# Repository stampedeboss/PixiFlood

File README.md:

# PixiFlood
PixiFlood LED Driver, Turn a 10w-100w floodlight Housing into a WS2811 Floodlight Pixel

DESCRIPTION:

A LED Driver that will allow a flood light to be controlled as a WS2811 Pixel. Allows up to 
170 flood lights to be controlled with a single universe. 

My goal was to enable placement of a flood light without having to deal with different controllers or 
wiring needs. By using WS2811, place a flood light at the beginning or end of a pixel string and maintain 
complete control. 

Version 2 and Version 3 introduced the concept of a built in ESPixelStick, which allows wireless connectitivy to communicate with the Floodlight.

Version 3:
Focused on delivering a single board designed to support any wattage of LED from 10w to 100w.
This objective required the design to no longer include direct attachment of the LED to the PCB, it is to 
be connected via wires to allow for the wide arrangement of LED sizes and pin spacings.

The previous designs relied on linear voltage regulators since the voltage reduction was acceptable going 
from 12v to 5v.  With the use of higher wattage LEDs, voltage requirements are much greater required changing
the 5v voltage regulator circuitry to a switching model to eliminate the overheating of the previous design.

The PT4115 specifications are unacceptable to anything above a 20w LED, as such beginning with 3.0 the LED
Driver is being switched out for an AL8862 and the supporting components have been modified to support that
new IC.

This new design includes the addition of a sidecar that contains ESPixelStick capabilities.  Using the sidecar
and an ESP-01 the floodlight can be driven wirelessly.

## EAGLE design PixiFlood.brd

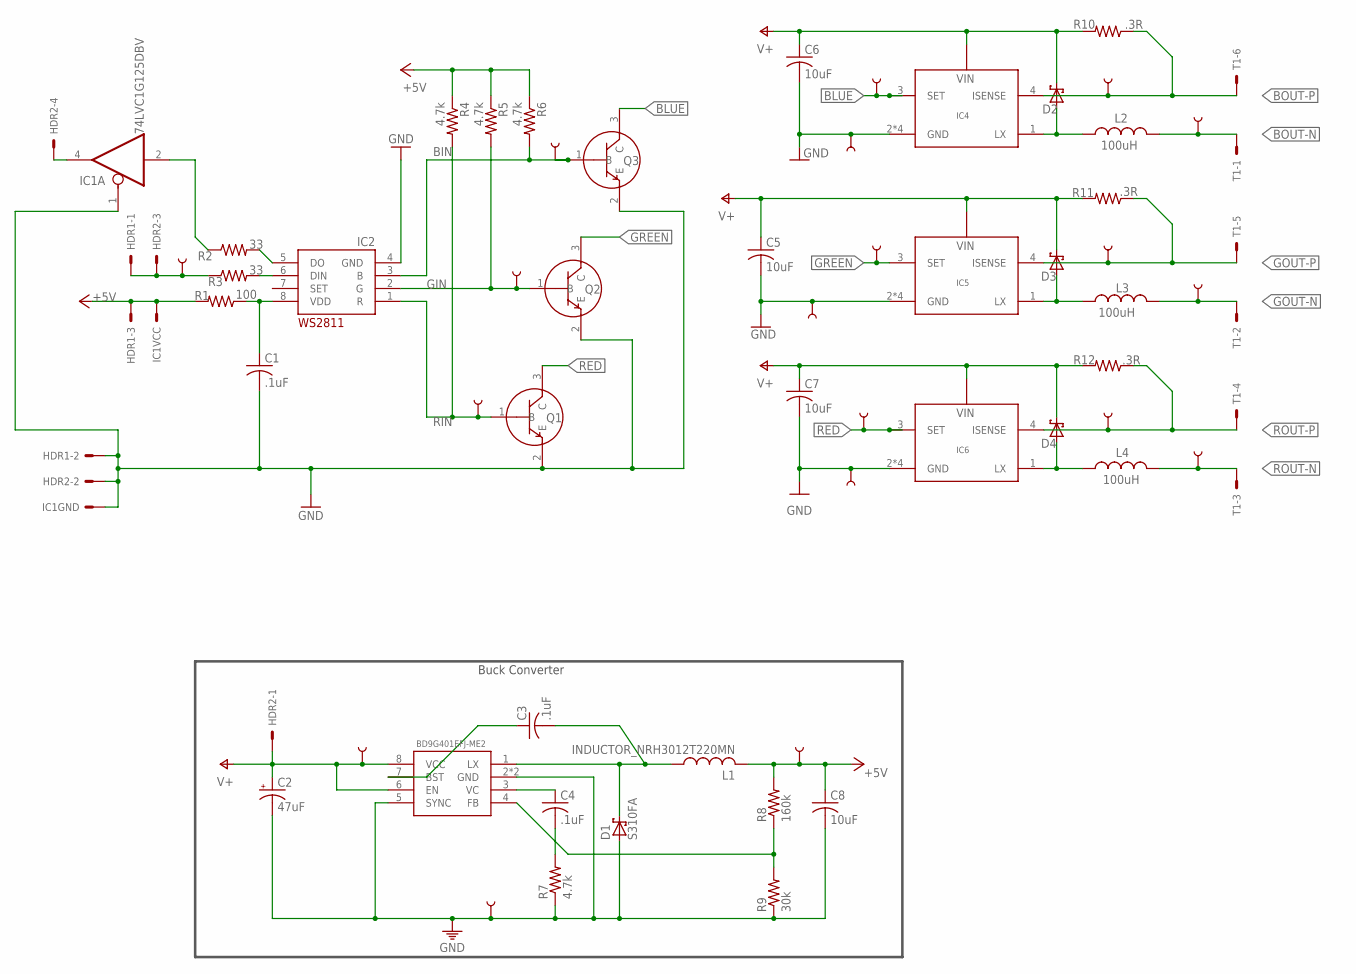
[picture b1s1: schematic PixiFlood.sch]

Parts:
C1, C3, C4: .1uF; C0805
C2: 47uF; UD-6,3X7,7_NICHICON
C5, C6, C7, C8: 10uF; C1206
D1, D2, D3, D4: S310FA; SOD-123FL
HDR1: M03FEMALE; 1X03_FEMALE
HDR2: M04STD; 1X04
IC1: 74LVC1G125DBV; SOT23-5
IC2: WS2811SOP8; SO08-P-1.27
IC3: BD9G401EFJ-ME2; SOIC127P600X100-9N
IC4, IC5, IC6: AL-8861SOT89-5; SOT89-5
L1: INDUCTOR_NRH3012T220MN; IND_TAIYO_NRH3012
L2, L3, L4: 100uH; SLF7045
Q1, Q2, Q3: BC847BC847; SOT23-3
R1: 100; R0805
R2, R3: 33; R0805
R4, R5, R6, R7: 4.7k; R0805
R8: 160k; R0805
R9: 30k; R0805
R10, R11, R12: .3R; R1210
T1: M06SIP; 1X06
TP1: ROUT-N; TP-1
TP2: GOUT-N; TP-1
TP3: BOUT-N; TP-1
TP4: RED; TP-1
TP5: BLUE; TP-1
TP6: GREEN; TP-1
TP7: BOUT-P; TP-1
TP8: GOUT-P; TP-1
TP9: ROUT-R; TP-1
TP11: RIN; TP-1
TP12: VIN; TP-1
TP13: DIN; TP-1
TP14, TP19, TP20, TP23: GND; TP-1
TP15: 5V; TP-1
TP21: BIN; TP-1
TP22: GIN; TP-1

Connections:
+5V: C8.1, HDR1.5, IC1.5 (S), L1.2, R1.2, R4.1, R5.1, R6.1, R8.2, TP15.P$1
BIN: IC2.3 (B), Q3.1 (B), R6.2, TP21.P$1
BLUE: IC4.3 (SET), Q3.3 (C), TP5.P$1
BOUT-N: L2.2, T1.1, TP3.P$1
BOUT-P: IC4.4 (ISENSE), R10.1, T1.6, TP7.P$1
DIN-IN: HDR1.1, HDR2.3, R3.1, TP13.P$1
DO: HDR2.4, IC1.4 (O)
GIN: IC2.2 (G), Q2.1 (B), R5.2, TP22.P$1
GND: C1.2, C2.-, C5.2, C6.2, C7.2, C8.2, D1.A, HDR1.3, HDR2.2, IC1.1 (OE), IC1.3 (S), IC2.4 (GND), IC3.2 (GND), IC3.5 (SYNC), IC3.9 (GND), IC4.2 (GND), IC4.2@1 (GND), IC4.2@2 (GND), IC4.2@3 (GND), IC5.2 (GND), IC5.2@1 (GND), IC5.2@2 (GND), IC5.2@3 (GND), IC6.2 (GND), IC6.2@1 (GND), IC6.2@2 (GND), IC6.2@3 (GND), Q1.2 (E), Q2.2 (E), Q3.2 (E), R7.1, R9.1, TP14.P$1, TP19.P$1, TP20.P$1, TP23.P$1
GOUT-N: L3.2, T1.2, TP2.P$1
GOUT-P: IC5.4 (ISENSE), R11.1, T1.5, TP8.P$1
GREEN: IC5.3 (SET), Q2.3 (C), TP6.P$1
unnamed: C4.1, IC3.3 (VC)
unnamed: D4.A, IC6.1 (LX), L4.1
unnamed: C3.2, D1.C, IC3.1 (LX), L1.1
unnamed: IC1.2 (I), R2.1
unnamed: D3.A, IC5.1 (LX), L3.1
unnamed: IC2.5 (DO), R2.2
unnamed: IC2.6 (DIN), R3.2
unnamed: C4.2, R7.2
unnamed: D2.A, IC4.1 (LX), L2.1
unnamed: IC3.4 (FB), R8.1, R9.2
unnamed: C3.1, IC3.7 (BST)
RED: IC6.3 (SET), Q1.3 (C), TP4.P$1
RIN: IC2.1 (R), Q1.1 (B), R4.2, TP11.P$1
ROUT-N: L4.2, T1.3, TP1.P$1
ROUT-P: IC6.4 (ISENSE), R12.1, T1.4, TP9.P$1
V+: C2.+, C5.1, C6.1, C7.1, D2.C, D3.C, D4.C, HDR2.1, IC3.6 (EN), IC3.8 (VCC), IC4.5 (VIN), IC5.5 (VIN), IC6.5 (VIN), R10.2, R11.2, R12.2, TP12.P$1
VDD: C1.1, IC2.8 (VDD), R1.1

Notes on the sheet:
Buck Converter

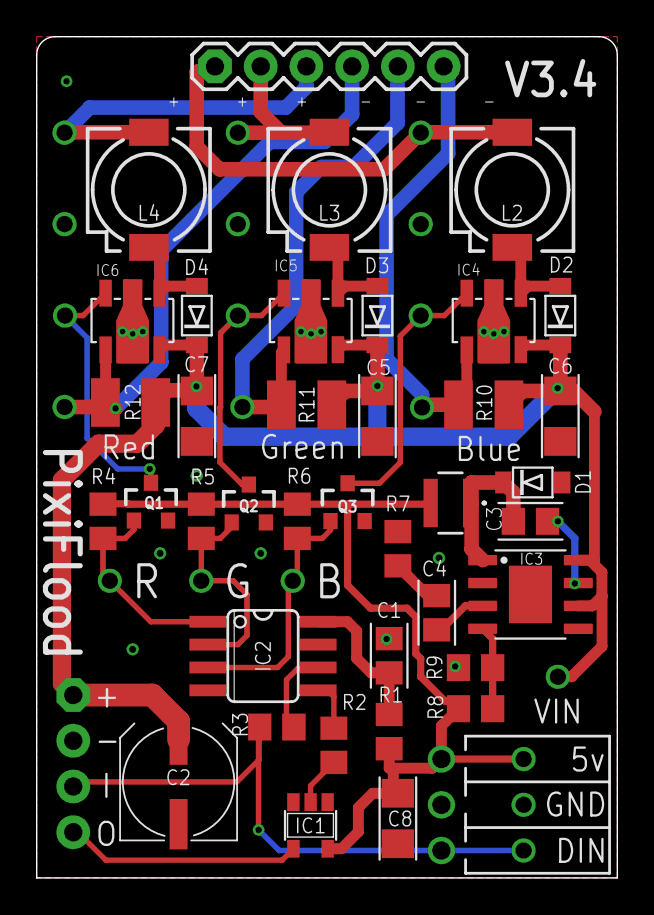
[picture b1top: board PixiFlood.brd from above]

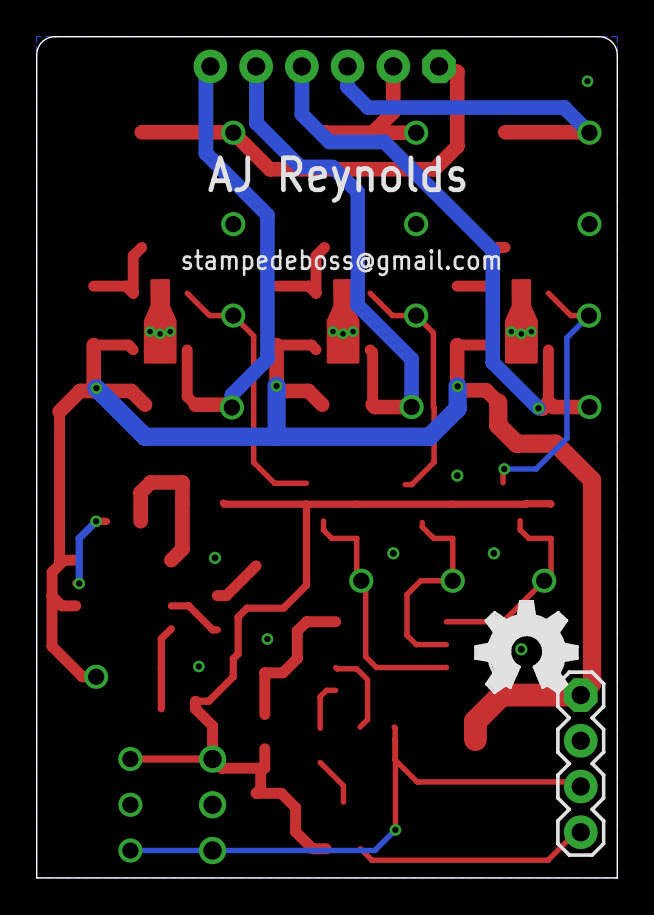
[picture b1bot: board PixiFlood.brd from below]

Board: 2 copper layers, 32.3 x 46.7 mm, 60 parts (2 on the bottom side), 29 nets.

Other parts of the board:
LOGO: OSHW_FILLX200_NOTEXT

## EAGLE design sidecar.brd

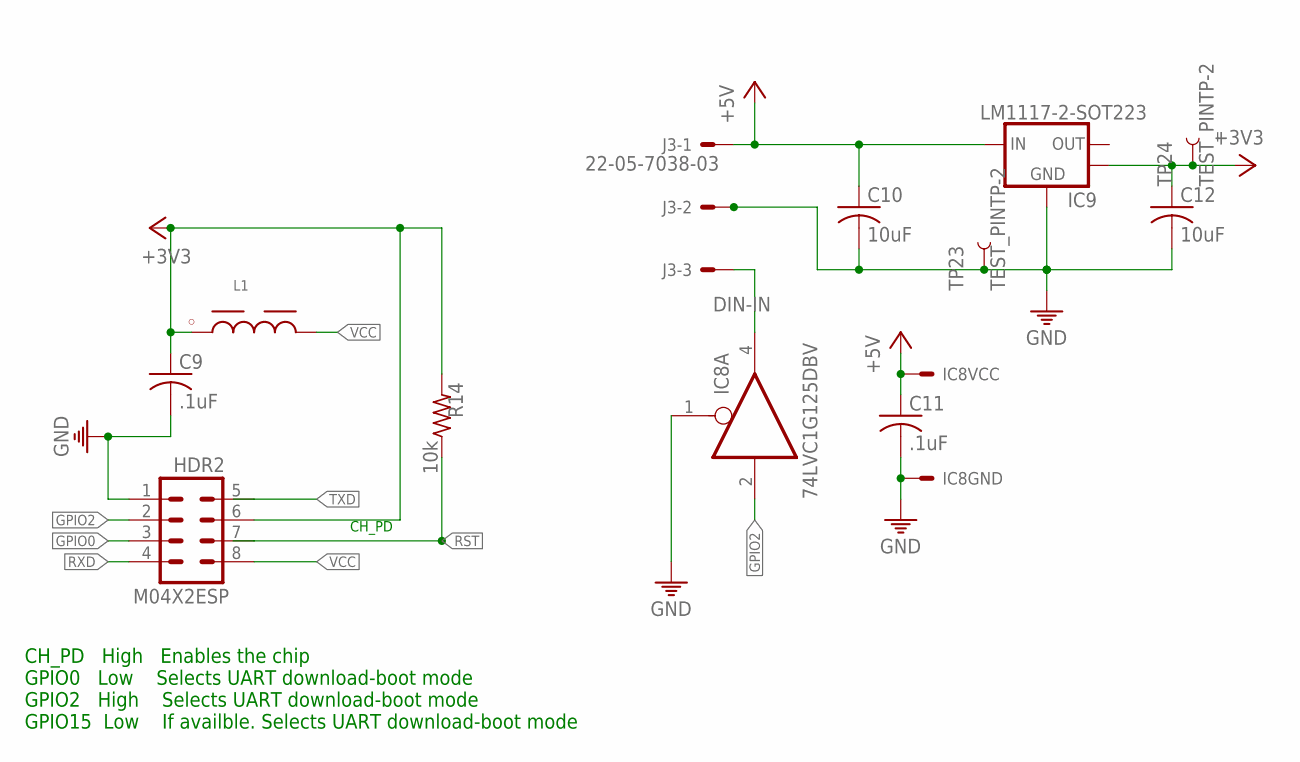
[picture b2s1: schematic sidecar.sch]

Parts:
C9, C11: .1uF; C0805
C10, C12: 10uF; C0805
HDR2: M04X2ESP; 2X4-ESP
IC8: 74LVC1G125DBV; SOT23-5
IC9: LM1117-2-SOT223; SOT-223-3
J3: 22-05-7038-03; 7395-03
L1: WE-CBA_0805_782851102_WB/HS; WE-CBA_0805(W=3)
R14: 10k; R0805
TP23, TP24: TEST_PINTP-2; TP-2

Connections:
+3V3: C9.1, C12.1, HDR2.6, IC9.4 (HEATSINK), L1.1, R14.2, TP24.P$1
+5V: C10.1, C11.1, IC8.5 (S), IC9.3 (VIN), J3.1
DIN-IN: IC8.4 (O), J3.3
GND: C9.2, C10.2, C11.2, C12.2, HDR2.1, IC8.1 (OE), IC8.3 (S), IC9.1 (GND), J3.2, TP23.P$1
GPIO0: HDR2.3
GPIO2: HDR2.2, IC8.2 (I)
RST: HDR2.7, R14.1
RXD: HDR2.4
TXD: HDR2.5
VCC: HDR2.8, L1.2

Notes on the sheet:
CH_PD High Enables the chip GPIO0 Low Selects UART download-boot mode GPIO2 High Selects UART download-boot mode GPIO15 Low If availble. Selects UART download-boot mode
CH_PD

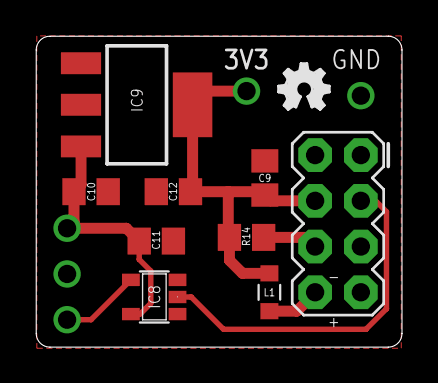
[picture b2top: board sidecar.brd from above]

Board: 2 copper layers, 20.3 x 17.3 mm, 13 parts (1 on the bottom side), 7 nets.

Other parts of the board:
U$8: OSHW_FILLX100_NOTEXT

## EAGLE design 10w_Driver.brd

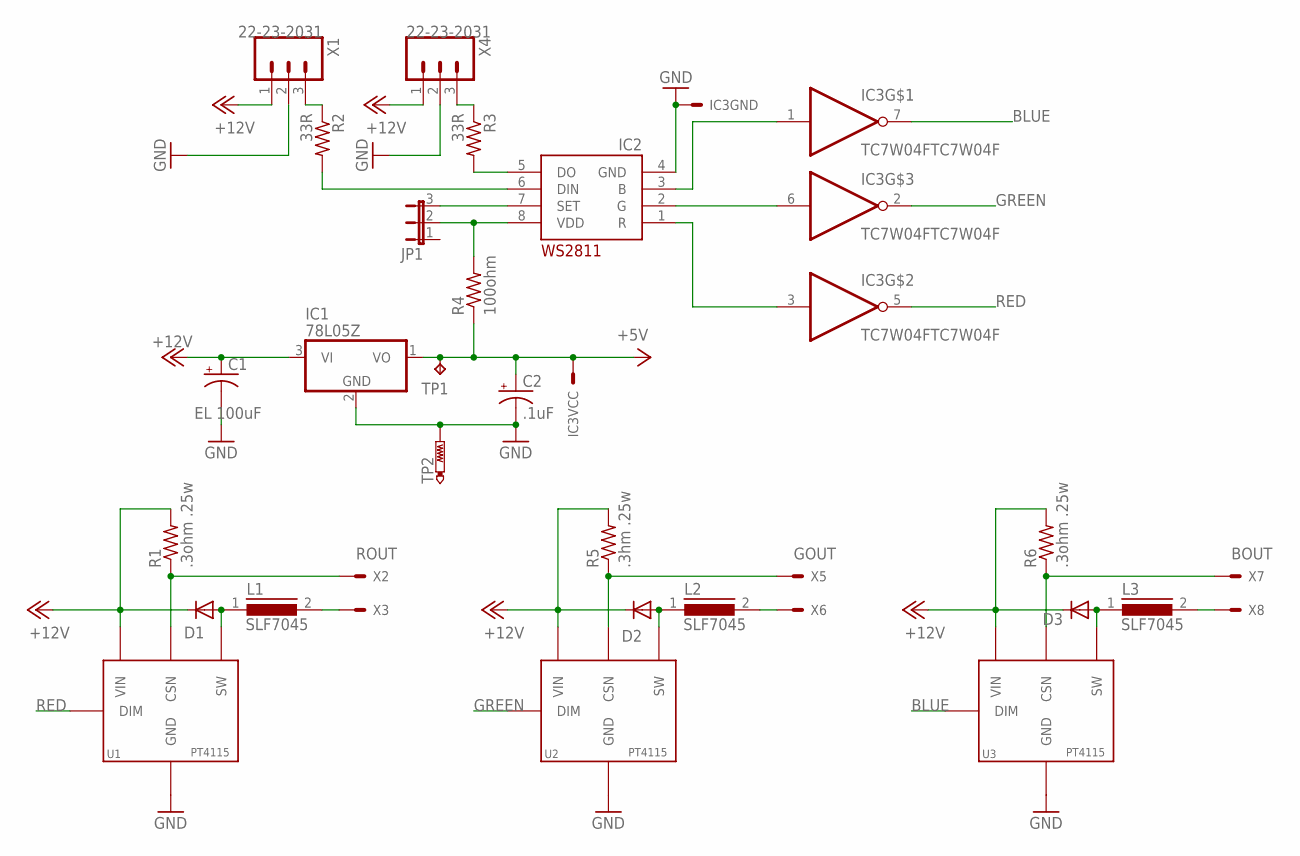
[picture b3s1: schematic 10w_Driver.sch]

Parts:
C1: EL 100uF; TT2D6L
C2: .1uF; B45181A
D1, D2, D3: DIODE-DO07; DO07
IC1: 78L05Z; TO92
IC2: WS2811-SOP8; SO08-SKINNYPADS
IC3: TC7W04FTC7W04F; SO08
JP1: JP2E; JP2
L1, L2, L3: SLF7045
R1, R6: .3ohm .25w; R1206
R2, R3: 33R; M0805
R4: 100ohm; M0805
R5: .3hm .25w; M1206
TP1: TPB2,54; B2,54
TP2: PTR1TP20SQ; TP20SQ
U1, U2, U3: PT4115PT4115B89E; SOT89-5
X1, X4: 22-23-2031
X2, X3, X5, X6, X7, X8: LED-PAD

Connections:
+5V: C2.+, IC1.1 (VO), IC3.8 (S), R4.1, TP1.TP
+12V: C1.+, D1.C, D2.C, D3.C, IC1.3 (VI), R1.2, R5.2, R6.2, U1.5 (VIN), U2.5 (VIN), U3.5 (VIN), X1.1, X4.1
BLUE: IC3.7 (O), U3.3 (DIM)
BOUT: R6.1, U3.4 (CSN), X7.P$1@1, X7.P$1@2, X7.P$1@3
GND: C1.-, C2.-, IC1.2 (GND), IC2.4 (GND), IC3.4 (S), TP2.TP, U1.2 (GND), U1.2A (GND), U1.2A@1 (GND), U1.2A@2 (GND), U1.2A@3 (GND), U1.2A@4 (GND), U2.2 (GND), U2.2A (GND), U2.2A@1 (GND), U2.2A@2 (GND), U2.2A@3 (GND), U2.2A@4 (GND), U3.2 (GND), U3.2A (GND), U3.2A@1 (GND), U3.2A@2 (GND), U3.2A@3 (GND), U3.2A@4 (GND), X1.2, X4.2
GOUT: R5.1, U2.4 (CSN), X5.P$1@1, X5.P$1@2, X5.P$1@3
GREEN: IC3.2 (O), U2.3 (DIM)
unnamed: D1.A, L1.1, U1.1 (SW)
unnamed: D3.A, L3.1, U3.1 (SW)
unnamed: L1.2, X3.P$1@1, X3.P$1@2, X3.P$1@3
unnamed: R3.1, X4.3
unnamed: D2.A, L2.1, U2.1 (SW)
unnamed: R2.1, X1.3
unnamed: IC2.5 (DO), R3.2
unnamed: IC2.6 (DIN), R2.2
unnamed: L2.2, X6.P$1@1, X6.P$1@2, X6.P$1@3
unnamed: L3.2, X8.P$1@1, X8.P$1@2, X8.P$1@3
unnamed: IC2.8 (VDD), JP1.2, R4.2
unnamed: IC2.1 (R), IC3.3 (I)
unnamed: IC2.3 (B), IC3.1 (I)
unnamed: IC2.7 (SET), JP1.3
unnamed: IC2.2 (G), IC3.6 (I)
RED: IC3.5 (O), U1.3 (DIM)
ROUT: R1.1, U1.4 (CSN), X2.P$1@1, X2.P$1@2, X2.P$1@3

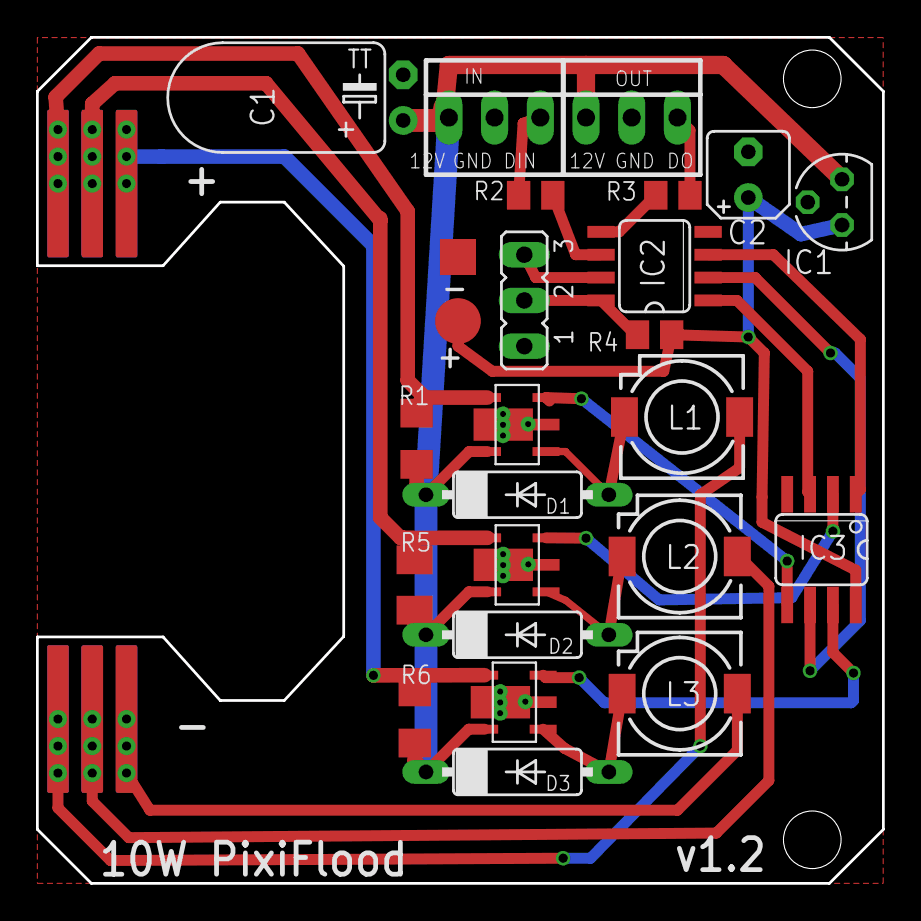
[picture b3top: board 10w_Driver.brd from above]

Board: 2 copper layers, 47.0 x 47.0 mm, 31 parts (0 on the bottom side), 24 nets.

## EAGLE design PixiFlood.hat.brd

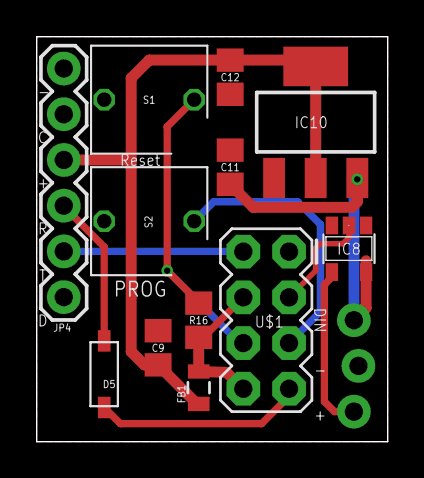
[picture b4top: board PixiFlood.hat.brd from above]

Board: 2 copper layers, 19.5 x 22.5 mm, 13 parts (1 on the bottom side), 11 nets.

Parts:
C9, C11, C12: C0805
D5: 1N4148; SOD-123
FB1: FB; 0805
IC8: 74LVC1G125DBV; SOT23-5
IC10: LM1117-2-SOT223; SOT-223-3
JP3: 1X03_LOCK
JP4: 1X06
R16: 10k; R0805
S1, S2: TACT_5MM
U$1: M04X2ESP; 2X4-ESP

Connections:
+3V3: C9.1, C12.1, FB1.1, IC10.2, IC10.4, JP4.3
+5V: C11.1, IC8.5, IC10.3, JP3.1
DIN-IN: IC8.4, JP3.3
GND: C9.2, C11.2, C12.2, IC8.1, IC8.3, IC10.1, JP3.2, JP4.1, S1.2, S2.2, U$1.1
GPIO0: S2.1, U$1.3
GPIO2: IC8.2, U$1.2
unnamed: D5.C, JP4.4
RST: R16.1, S1.1, U$1.7
RXD: D5.A, U$1.4
TXD: JP4.5, U$1.5
VCC: FB1.2, R16.2, U$1.6, U$1.8

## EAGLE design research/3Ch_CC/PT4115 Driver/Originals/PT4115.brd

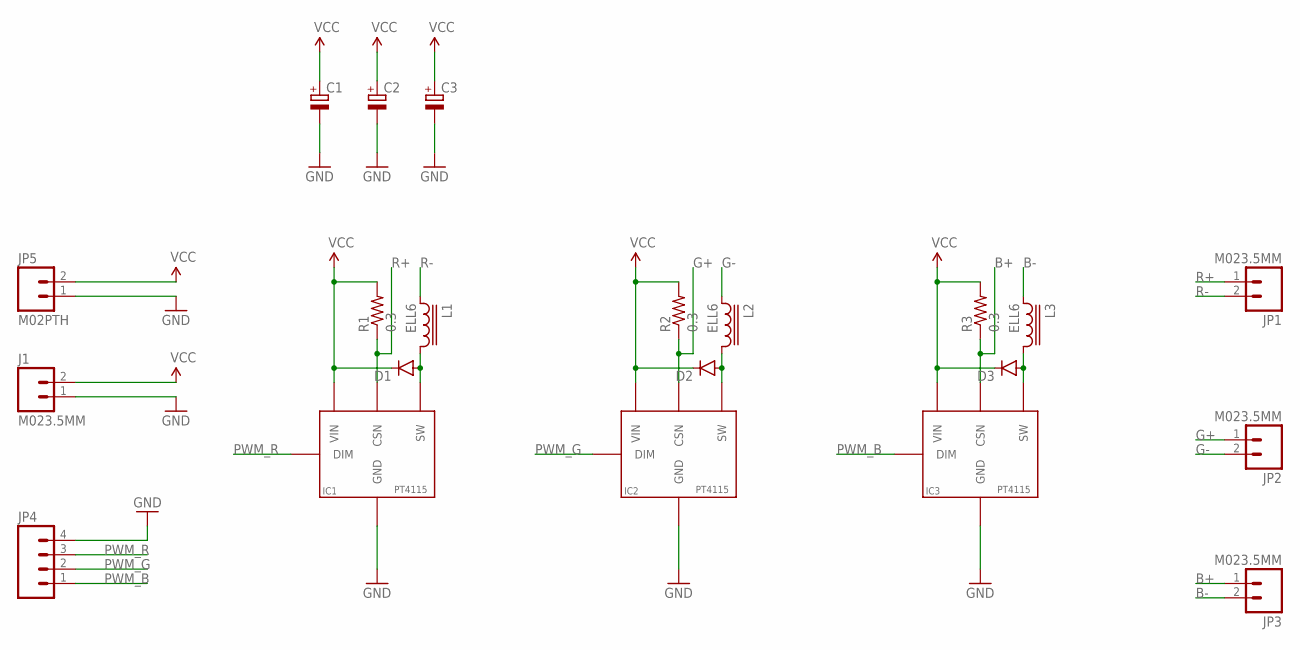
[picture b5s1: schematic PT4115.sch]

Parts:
C1, C2, C3: CPOL-EUD/7343-31R; D/7343-31R
D1, D2, D3: DIODESMA-KIT; SMA-DIODE-KIT
IC1, IC2, IC3: PT4115PT4115B89E; SOT89-5
J1: M023.5MM; SCREWTERMINAL-3.5MM-2
JP1, JP2, JP3: M023.5MM; SCREWTERMINAL-3.5MM-2
JP4: M04LONGPADS; 1X04_LONGPADS
JP5: M02PTH; 1X02
L1, L2, L3: ELL6
R1, R2, R3: 0.3; 0805

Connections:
B+: IC3.4 (CSN), JP3.1, R3.1
B-: JP3.2, L3.1
G+: IC2.4 (CSN), JP2.1, R2.1
G-: JP2.2, L2.1
GND: C1.-, C2.-, C3.-, IC1.2 (GND), IC1.2A (GND), IC2.2 (GND), IC2.2A (GND), IC3.2 (GND), IC3.2A (GND), J1.1, JP4.4, JP5.1
unnamed: D1.A, IC1.1 (SW), L1.2
unnamed: D2.A, IC2.1 (SW), L2.2
unnamed: D3.A, IC3.1 (SW), L3.2
PWM_B: IC3.3 (DIM), JP4.1
PWM_G: IC2.3 (DIM), JP4.2
PWM_R: IC1.3 (DIM), JP4.3
R+: IC1.4 (CSN), JP1.1, R1.1
R-: JP1.2, L1.1
VCC: C1.+, C2.+, C3.+, D1.C, D2.C, D3.C, IC1.5 (VIN), IC2.5 (VIN), IC3.5 (VIN), J1.2, JP5.2, R1.2, R2.2, R3.2

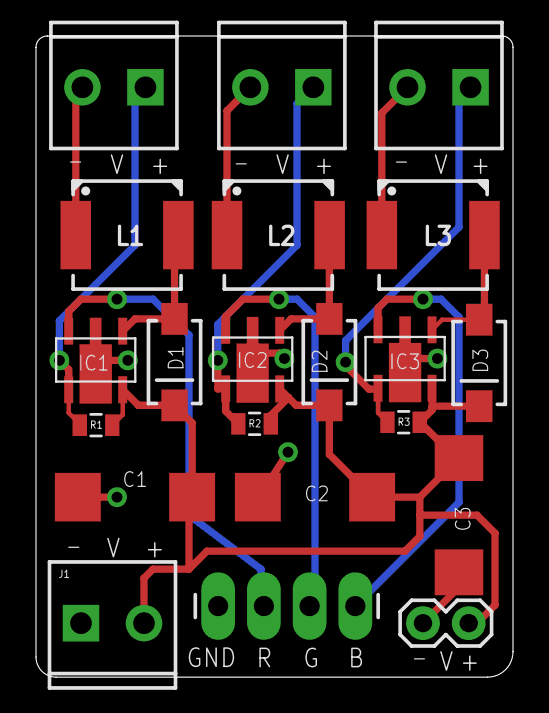
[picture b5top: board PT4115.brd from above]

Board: 2 copper layers, 26.5 x 35.6 mm, 21 parts (0 on the bottom side), 14 nets.

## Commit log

2019-05-26 Initial Design with ws2811
2019-05-26 Final 1.1
2019-05-26 Final 1.1 with Inverter
2019-05-26 Reworked Inverter Layout
2019-05-26 Reworked Layout
2019-05-26 Reworked and retitled to PixiFlood
2019-05-26 Reworked and retitled to PixiFlood SMD
2019-05-26 gitignore changes
2019-05-26 Reworking Sidecar
2019-05-26 Transistor version
2019-05-26 Modified testpoint drill size
2019-05-26 Panelized Boards
2019-05-27 Simplified the Design
2019-05-30 Cleaned up some labels
2019-05-30 Cleaned up transistors
2019-06-01 Changed Connector
2019-06-04 added adpater boards and changed pinout on led

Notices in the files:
parts and their libraries:
SparkFun-Passives: Licensing: CC v3.0 Share-Alike You are welcome to use this library for commercial purposes.
SparkFun-Connectors: Licensing: Creative Commons ShareAlike 4.0 International - https://creativecommons.org/licenses/by-sa/4.0
inductor-panasonic: Copyright (C) 2009, Bob Starr
